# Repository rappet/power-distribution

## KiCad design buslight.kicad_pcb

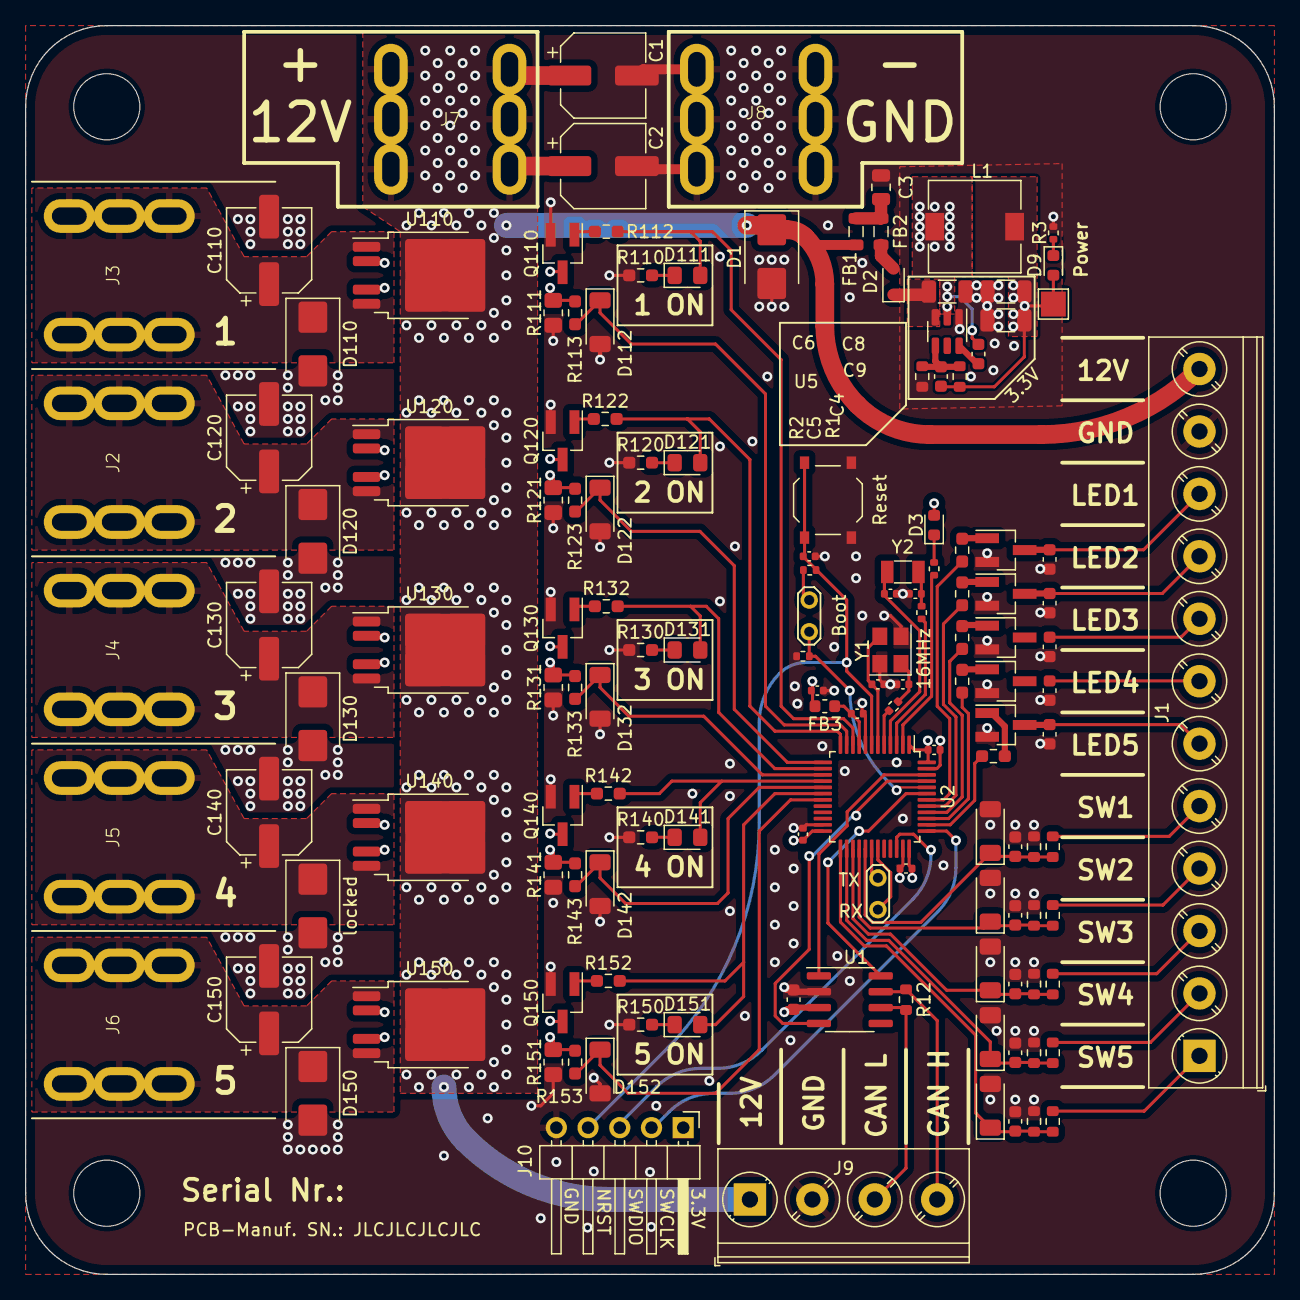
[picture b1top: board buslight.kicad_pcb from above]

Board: 4 copper layers, 100.0 x 100.0 mm, 144 parts (0 on the bottom side), 90 nets.

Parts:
C1, C2, C110, C120, C130, C140, C150: 100uF 35V; CP_Elec_6.3x7.7
C3: 100n; C_0805_2012Metric
C4, C7, C20, C21, C22, C23, C24: 100n; C_0603_1608Metric
C5: 47p; C_0603_1608Metric
C6: 10uF; C_1206_3216Metric
C8, C9: 47u; C_1206_3216Metric
C10, C11, C12, C13, C14, C19: 100n; C_0402_1005Metric
C15, C16: 10p; C_0402_1005Metric
C17, C18: 18p; C_0402_1005Metric
C25, C26, C27, C28, C29: 1u 50V; C_0603_1608Metric
D1, D110, D120, D130, D150: SMBJ30CA; D_SMB
D2: 1N5819WS; D_SOD-323
D3, D9: RED; LED_0603_1608Metric
D20, D21, D22, D23, D24, D112, D122, D132, D142, D152: ZMM3V3-M; D_MiniMELF
D111, D121, D131, D141, D151: LED; LED_0805_2012Metric_Pad1.15x1.40mm_HandSolder
FB1, FB2: 100Ω@100MHz; L_0805_2012Metric
FB3: 600Ω@100MHz; L_0603_1608Metric
H1, H2, H3, H4: MountingHole; MountingHole_5.3mm_M5_ISO7380
J1: Screw_Terminal_01x12; TerminalBlock_Phoenix_PT-1,5-12-5.0-H_1x12_P5.00mm_Horizont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
J2, J3, J4, J5, J6, J7, J8: Screw_Terminal_01x01; T46004
J9: Screw_Terminal_01x04; TerminalBlock_Phoenix_PT-1,5-4-5.0-H_1x04_P5.00mm_Horizontal
J10: Conn_01x05_Pin; PinHeader_1x05_P2.54mm_Horizontal
L1: 10uH 39.6mΩ; L_7.3x7.3_H4.5
Q1, Q2, Q3, Q4, Q5, Q110, Q120, Q130, Q140, Q150: MMBT3904; SOT-23_Handsoldering
R1: 100k; R_0603_1608Metric
R2: 22k; R_0603_1608Metric
R3: 1kR; R_0402_1005Metric
R4, R6: 1k; R_0402_1005Metric
R10, R11: 0R; R_0402_1005Metric
R12: 120R; R_0603_1608Metric
R13: 10k; R_0402_1005Metric
R20, R21, R22, R23, R24, R110, R112, R113, R120, R122, R123, R130, R132, R133, R140, R142, R143, R150, R152, R153: 1k; R_0603_1608Metric_Pad0.98x0.95mm_HandSolder
R25, R26, R27, R28, R29: 3.3k; R_0603_1608Metric
R30, R31, R32, R33, R34: 1k; R_0603_1608Metric
R111, R121, R131, R141, R151: 220; R_0805_2012Metric_Pad1.20x1.40mm_HandSolder
SW2: Reset; SW_Push_1P1T_XKB_TS-1187A
TP1: TestPoint; TestPoint_Pad_2.0x2.0mm
TP2: UART; TestPoint_2Pads_Pitch2.54mm_Drill0.8mm
TP3: Boot0; TestPoint_2Pads_Pitch2.54mm_Drill0.8mm
U1: SN65HVD230; SOIC-8_3.9x4.9mm_P1.27mm
U2: STM32F103C8T6; LQFP-48_7x7mm_P0.5mm
U5: TPS54202; SOT-23-6
U110, U120, U130, U140, U150: BTS6143D; TO-252-4
Y1: 16MHz 9pF; Crystal_SMD_3225-4Pin_3.2x2.5mm
Y2: 32.768kHz 12.5pF; Crystal_SMD_3215-2Pin_3.2x1.5mm
locked: SMBJ30CA; D_SMB

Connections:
+3.3V: C5.2, C7.2, C8.1, C9.1, C10.1, C11.1, C12.1, C14.1, D3.2 (A), D9.2 (A), FB3.2, J10.1, L1.2, R1.1, R4.1, TP1.1, TP3.1, U1.3 (VCC), U2.1 (VBAT), U2.24 (VDD), U2.36 (VDD), U2.48 (VDD)
+12V: C6.1, D2.1 (K), U5.3 (VIN)
+BATT: C1.1, C2.1, D1.1 (A1), FB1.1, J1.12, J7.1, J9.1, U110.3 (Vbb), U120.3 (Vbb), U130.3 (Vbb), U140.3 (Vbb), U150.3 (Vbb)
/Control/BOOT0: R13.2, TP3.2, U2.44 (BOOT0)
/Control/CAN_H: J9.4, R12.1, U1.7 (CANH)
/Control/CAN_L: J9.3, R12.2, U1.6 (CANL)
/Control/CAN_RX: U1.4 (R), U2.45 (PB8)
/Control/CAN_Rs: U1.8 (Rs), U2.43 (PB7)
/Control/CAN_TX: U1.1 (D), U2.46 (PB9)
/Control/LED: R6.2, U2.2 (PC13)
/Control/NRST: C19.1, J10.4, R4.2, SW2.2, U2.7 (NRST)
/Control/OSC32_IN: R11.2, U2.3 (PC14)
/Control/OSC32_OUT: C18.1, U2.4 (PC15), Y2.2
/Control/OSC_IN: R10.2, U2.5 (PD0)
/Control/OSC_OUT: C16.1, U2.6 (PD1), Y1.3
/Control/SWCLK: J10.2, U2.37 (PA14)
/Control/SWDIO: J10.3, U2.34 (PA13)
/IO Ports/LED_1_Conn: C20.1, J1.10, Q1.3 (C)
/IO Ports/LED_2_Conn: C21.2, J1.9, Q2.3 (C)
/IO Ports/LED_3_Conn: C22.2, J1.8, Q3.3 (C)
/IO Ports/LED_4_Conn: C23.2, J1.7, Q4.3 (C)
/IO Ports/LED_5_Conn: C24.2, J1.6, Q5.3 (C)
/IO Ports/SW_1_Conn: J1.5, R30.2
/IO Ports/SW_2_Conn: J1.4, R31.2
/IO Ports/SW_3_Conn: J1.3, R32.2
/IO Ports/SW_4_Conn: J1.2, R33.2
/IO Ports/SW_5_Conn: J1.1, R34.2
/Power supply/BOOT_3.3: C4.1, U5.6 (BOOT)
/Power supply/FB_3.3: C5.1, R1.2, R2.1, U5.4 (FB)
/Power supply/SW_3.3: C4.2, L1.1, U5.2 (SW)
/Switch 1/IN_Inverted: Q110.3 (C), U110.2 (IN)
/Switch 1/OUT: C110.1, D110.1 (A1), J3.1, U110.1 (OUT), U110.5 (OUT)
/Switch 2/IN_Inverted: Q120.3 (C), U120.2 (IN)
/Switch 2/OUT: C120.1, D120.1 (A1), J2.1, U120.1 (OUT), U120.5 (OUT)
/Switch 3/IN_Inverted: Q130.3 (C), U130.2 (IN)
/Switch 3/OUT: C130.1, D130.1 (A1), J4.1, U130.1 (OUT), U130.5 (OUT)
/Switch 4/IN_Inverted: Q140.3 (C), U140.2 (IN)
/Switch 4/OUT: C140.1, J5.1, U140.1 (OUT), U140.5 (OUT), locked.1 (A1)
/Switch 5/IN_Inverted: Q150.3 (C), U150.2 (IN)
/Switch 5/OUT: C150.1, D150.1 (A1), J6.1, U150.1 (OUT), U150.5 (OUT)
EN_1: D111.2 (A), R112.2, U2.10 (PA0)
EN_2: D121.2 (A), R122.2, U2.12 (PA2)
EN_3: D131.2 (A), R132.2, U2.14 (PA4)
EN_4: D141.2 (A), R142.2, U2.16 (PA6)
EN_5: D151.2 (A), R152.2, U2.18 (PB0)
GND: C1.2, C2.2, C3.2, C6.2, C7.1, C8.2, C9.2, C10.2, C11.2, C12.2, C13.2, C14.2, C15.2, C16.2, C17.2, C18.2, C19.2, C20.2, C21.1, C22.1, C23.1, C24.1, C25.2, C26.2, C27.2, C28.2, C29.2, C110.2, C120.2, C130.2, C140.2, C150.2, D1.2 (A2), D20.2 (A), D21.2 (A), D22.2 (A), D23.2 (A), D24.2 (A), D110.2 (A2), D112.2 (A), D120.2 (A2), D122.2 (A), D130.2 (A2), D132.2 (A), D142.2 (A), D150.2 (A2), D152.2 (A), J1.11, J8.1, J9.2, J10.5, Q1.2 (E), Q2.2 (E), Q3.2 (E), Q4.2 (E), Q5.2 (E), Q110.2 (E), Q120.2 (E), Q130.2 (E), Q140.2 (E), Q150.2 (E), R2.2, R3.2, R13.1, R25.2, R26.2, R27.2, R28.2, R29.2, R110.1, R111.2, R120.1, R121.2, R130.1, R131.2, R140.1, R141.2, R150.1, R151.2, SW2.1, U1.2 (GND), U2.8 (VSSA), U2.23 (VSS), U2.35 (VSS), U2.47 (VSS), U5.1 (GND), Y1.2, Y1.4, locked.2 (A2)
LED_1: R20.2, U2.42 (PB6)
LED_2: R21.2, U2.41 (PB5)
LED_3: R22.2, U2.40 (PB4)
LED_4: R23.2, U2.39 (PB3)
LED_5: R24.2, U2.38 (PA15)
unnamed: C3.1, FB1.2, FB2.1
unnamed: C15.1, R10.1, Y1.1
unnamed: C17.1, R11.1, Y2.1
unnamed: D2.2 (A), FB2.2
unnamed: D3.1 (K), R6.1
unnamed: D9.1 (K), R3.1
unnamed: D111.1 (K), R110.2
unnamed: D121.1 (K), R120.2
unnamed: D131.1 (K), R130.2
unnamed: D141.1 (K), R140.2
unnamed: D151.1 (K), R150.2
unnamed: Q1.1 (B), R20.1
unnamed: Q2.1 (B), R21.1
unnamed: Q3.1 (B), R22.1
unnamed: Q4.1 (B), R23.1
unnamed: Q5.1 (B), R24.1
unnamed: Q110.1 (B), R112.1
unnamed: Q120.1 (B), R122.1
unnamed: Q130.1 (B), R132.1
unnamed: Q140.1 (B), R142.1
unnamed: Q150.1 (B), R152.1
unnamed: R111.1, R113.1, U110.4 (IS)
unnamed: R121.1, R123.1, U120.4 (IS)
unnamed: R131.1, R133.1, U130.4 (IS)
unnamed: R141.1, R143.1, U140.4 (IS)
unnamed: R151.1, R153.1, U150.4 (IS)
RX: TP2.2, U2.31 (PA10)
SW_1: C25.1, D20.1 (K), R25.1, R30.1, U2.29 (PA8)
SW_2: C26.1, D21.1 (K), R26.1, R31.1, U2.28 (PB15)
SW_3: C27.1, D22.1 (K), R27.1, R32.1, U2.27 (PB14)
SW_4: C28.1, D23.1 (K), R28.1, R33.1, U2.26 (PB13)
SW_5: C29.1, D24.1 (K), R29.1, R34.1, U2.25 (PB12)
Sense_1: D112.1 (K), R113.2, U2.11 (PA1)
Sense_2: D122.1 (K), R123.2, U2.13 (PA3)
Sense_3: D132.1 (K), R133.2, U2.15 (PA5)
Sense_4: D142.1 (K), R143.2, U2.17 (PA7)
Sense_5: D152.1 (K), R153.2, U2.19 (PB1)
TX: TP2.1, U2.30 (PA9)
VDDA: C13.1, FB3.1, U2.9 (VDDA)

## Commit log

2023-07-17 Finalizing initial design
2023-07-18 Final touches
